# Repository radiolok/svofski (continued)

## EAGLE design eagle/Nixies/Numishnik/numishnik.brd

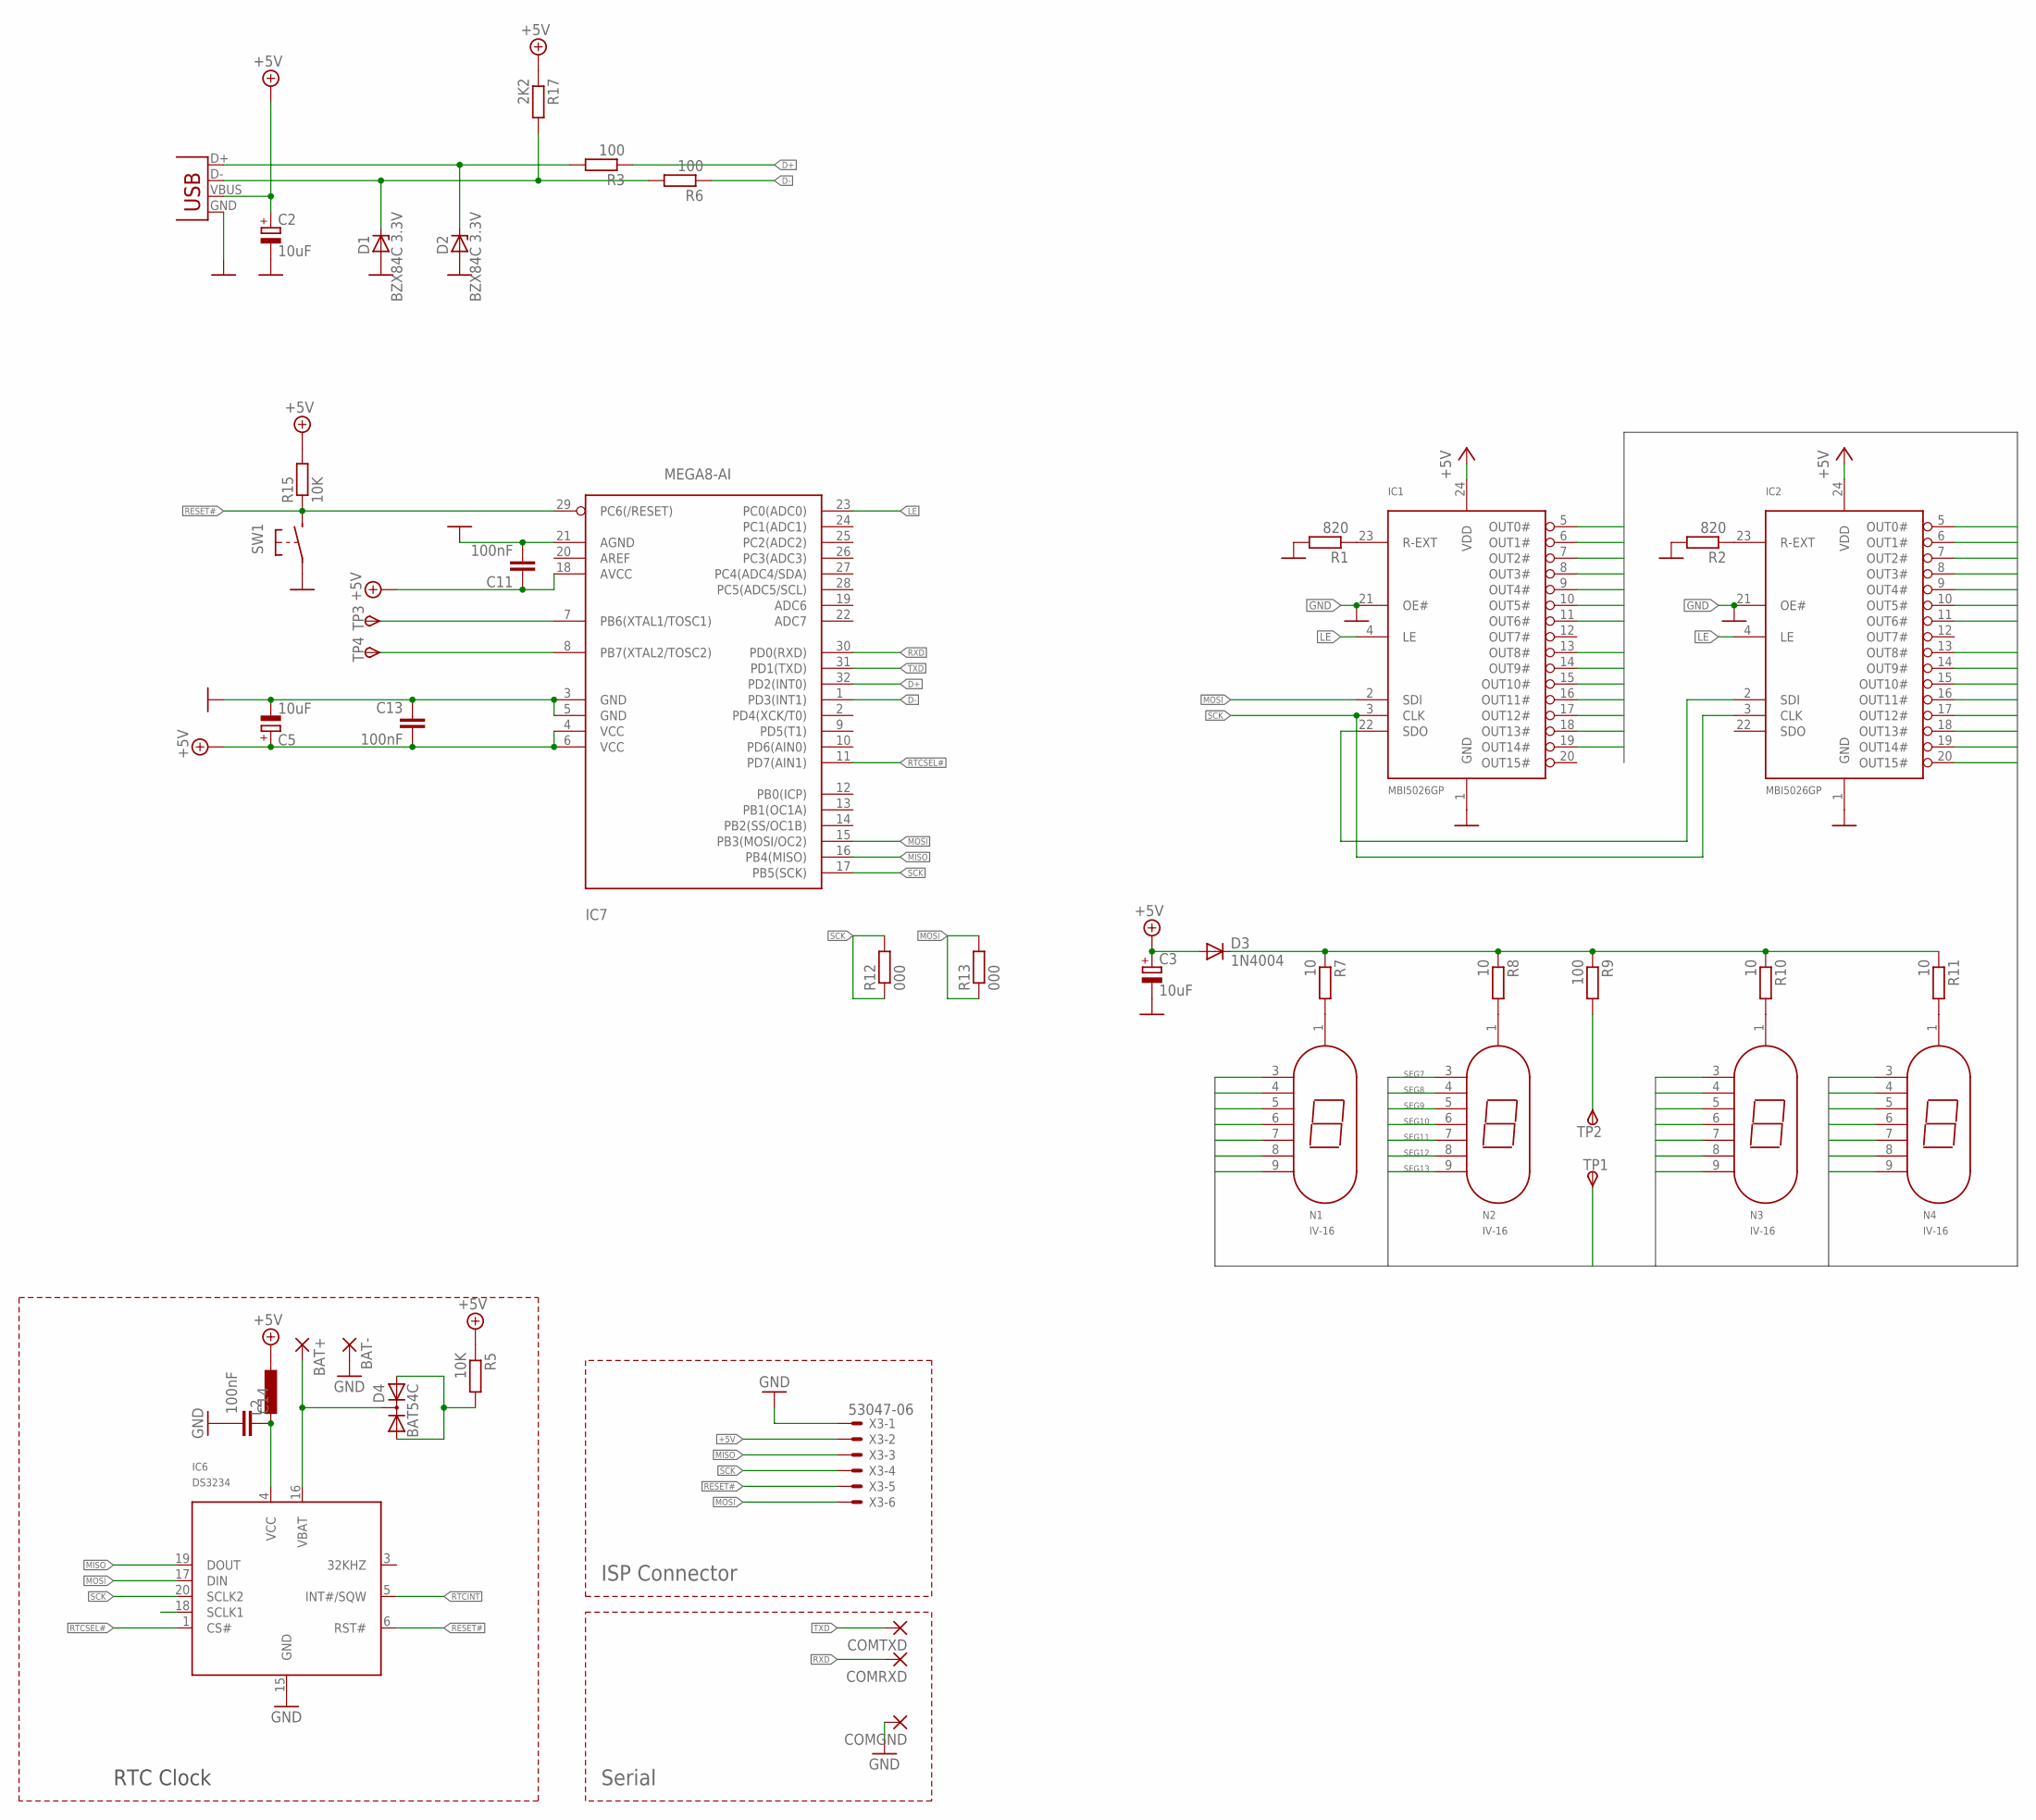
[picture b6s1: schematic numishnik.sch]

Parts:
BAT+: 1,6/0,8
BAT-: 1,6/0,8
C2, C3, C5: 10uF; SMC_B
C11, C13, C14: 100nF; C0603K
COMGND: 1,6/0,8
COMRXD: 1,6/0,8
COMTXD: 1,6/0,8
D1, D2: BZX84C 3.3V; TO236
D3: 1N4004; DO41-10
D4: BAT54C; SOT23
IC1, IC2: MBI5026GP; SSOP24-150
IC6: DS3234; SO-20DW
IC7: MEGA8-AI; TQFP32-08
L2: L-EUL3230M; L3230M
N1, N2, N3, N4: IV-16
R1, R2: 820; R0805-SVO
R3, R6, R9: 100; R0805-SVO
R5, R15: 10K; R0805-SVO
R7, R8, R10, R11: 10; R0805-SVO
R12, R13: 000; R0805-SVO
R17: 2K2; R0805-SVO
SW1: BUTTON-IT_1181; SW_IT1181
TP1, TP2, TP3, TP4: TPSPAD1-13; P1-13
X1: USB-MICROB
X3: 53047-06

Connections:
+5V: C2.+, C3.+, C5.+, C11.1, C13.2, D3.A, IC1.24 (VDD), IC2.24 (VDD), IC7.4 (VCC), IC7.6 (VCC), IC7.18 (AVCC), L2.1, R5.1, R15.2, R17.1, X1.VBUS, X3.2
D+: IC7.32 (PD2(INT0)), R3.1
D-: IC7.1 (PD3(INT1)), R6.1
DOT: IC2.20 (OUT15#), TP1.1
GND: BAT-.1, C2.-, C3.-, C5.-, C11.2, C13.1, C14.2, COMGND.1, D1.A, D2.A, IC1.1 (GND), IC1.21 (OE#), IC2.1 (GND), IC2.21 (OE#), IC6.15 (GND), IC7.3 (GND), IC7.5 (GND), IC7.21 (AGND), R1.2, R2.2, SW1.P$1 (P1), X1.GND, X3.1
LE: IC1.4 (LE), IC2.4 (LE), IC7.23 (PC0(ADC0))
MISO: IC6.19 (DOUT), IC7.16 (PB4(MISO)), X3.3
MOSI: IC1.2 (SDI), IC6.17 (DIN), IC7.15 (PB3(MOSI/OC2)), R13.1, R13.2, X3.6
MOSI#2: IC1.22 (SDO), IC2.2 (SDI)
unnamed: IC7.7 (PB6(XTAL1/TOSC1)), TP3.1
unnamed: R9.2, TP2.1
unnamed: N1.1, R7.2
unnamed: IC1.23 (R-EXT), R1.1
unnamed: IC2.23 (R-EXT), R2.1
unnamed: D1.C, R6.2, R17.2, X1.D-
unnamed: D2.C, R3.2, X1.D+
unnamed: BAT+.1, D4.3 (C), IC6.16 (VBAT)
unnamed: D4.1 (A1), D4.2 (A2), R5.2
unnamed: N2.1, R8.2
unnamed: N3.1, R10.2
unnamed: N4.1, R11.2
unnamed: D3.C, R7.1, R8.1, R9.1, R10.1, R11.1
RESET#: IC6.6 (RST#), IC7.29 (PC6(/RESET)), R15.1, SW1.P$2 (P2), X3.5
RTCINT: IC6.5 (INT#/SQW)
RTCSEL#: IC6.1 (CS#), IC7.11 (PD7(AIN1))
RTCVCC: C14.1, IC6.4 (VCC), L2.2
RXD: COMRXD.1, IC7.30 (PD0(RXD))
SCK: IC1.3 (CLK), IC2.3 (CLK), IC6.20 (SCLK2), IC7.17 (PB5(SCK)), R12.1, R12.2, X3.4
SEG0: IC1.11 (OUT6#), N1.3 (2)
SEG1: IC1.10 (OUT5#), N1.4 (3)
SEG2: IC1.9 (OUT4#), N1.5 (4)
SEG3: IC1.8 (OUT3#), N1.6 (5)
SEG4: IC1.7 (OUT2#), N1.7 (6)
SEG5: IC1.6 (OUT1#), N1.8 (7)
SEG6: IC1.5 (OUT0#), N1.9 (8)
SEG7: IC1.19 (OUT14#), N2.3 (2)
SEG8: IC1.18 (OUT13#), N2.4 (3)
SEG9: IC1.17 (OUT12#), N2.5 (4)
SEG10: IC1.16 (OUT11#), N2.6 (5)
SEG11: IC1.15 (OUT10#), N2.7 (6)
SEG12: IC1.14 (OUT9#), N2.8 (7)
SEG13: IC1.13 (OUT8#), N2.9 (8)
SEG14: IC2.11 (OUT6#), N3.3 (2)
SEG15: IC2.10 (OUT5#), N3.4 (3)
SEG16: IC2.9 (OUT4#), N3.5 (4)
SEG17: IC2.8 (OUT3#), N3.6 (5)
SEG18: IC2.7 (OUT2#), N3.7 (6)
SEG19: IC2.6 (OUT1#), N3.8 (7)
SEG20: IC2.5 (OUT0#), N3.9 (8)
SEG21: IC2.19 (OUT14#), N4.3 (2)
SEG22: IC2.18 (OUT13#), N4.4 (3)
SEG23: IC2.17 (OUT12#), N4.5 (4)
SEG24: IC2.16 (OUT11#), N4.6 (5)
SEG25: IC2.15 (OUT10#), N4.7 (6)
SEG26: IC2.14 (OUT9#), N4.8 (7)
SEG27: IC2.13 (OUT8#), N4.9 (8)
TXD: COMTXD.1, IC7.31 (PD1(TXD))
XTAL2: IC7.8 (PB7(XTAL2/TOSC2)), TP4.1

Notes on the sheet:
ISP Connector
Serial
RTC Clock

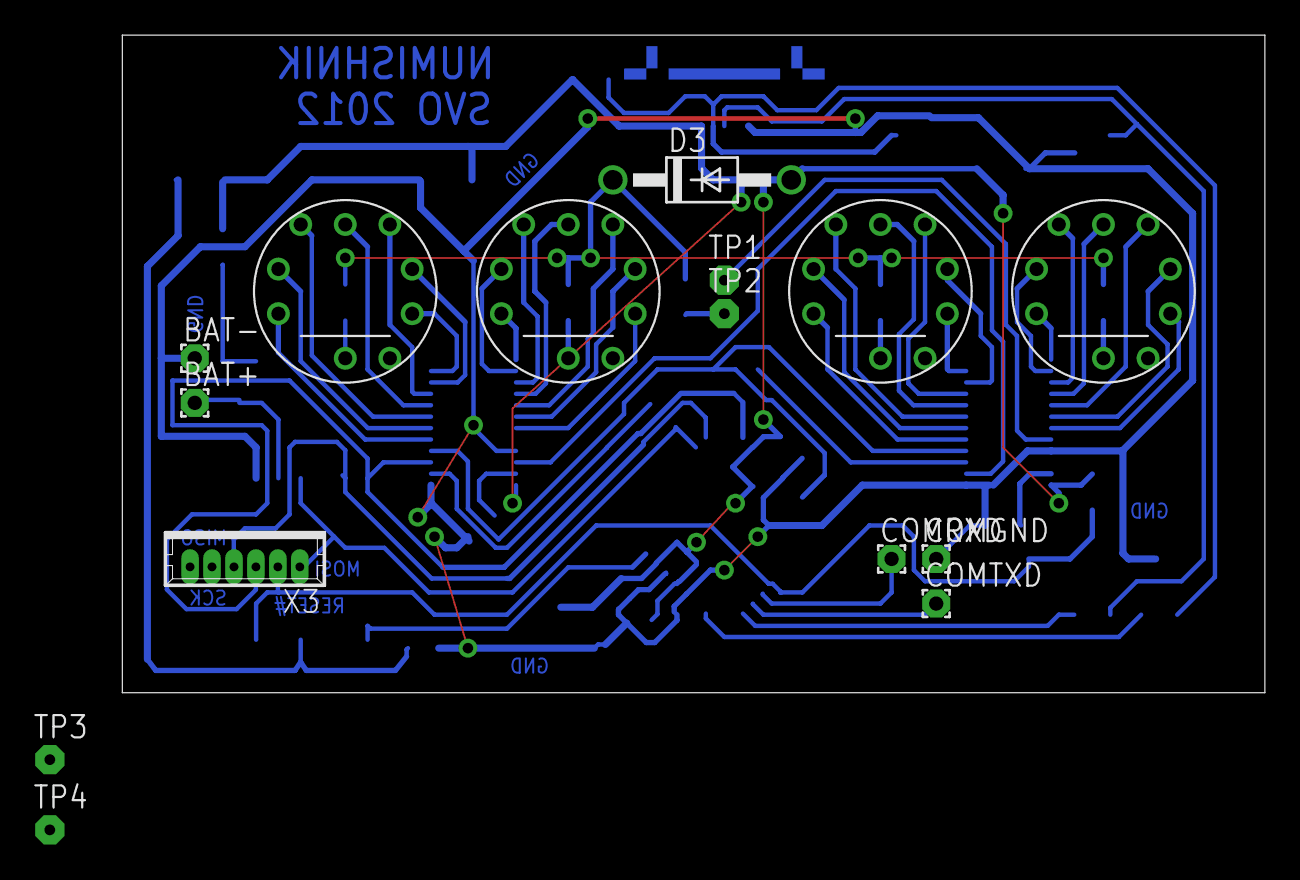
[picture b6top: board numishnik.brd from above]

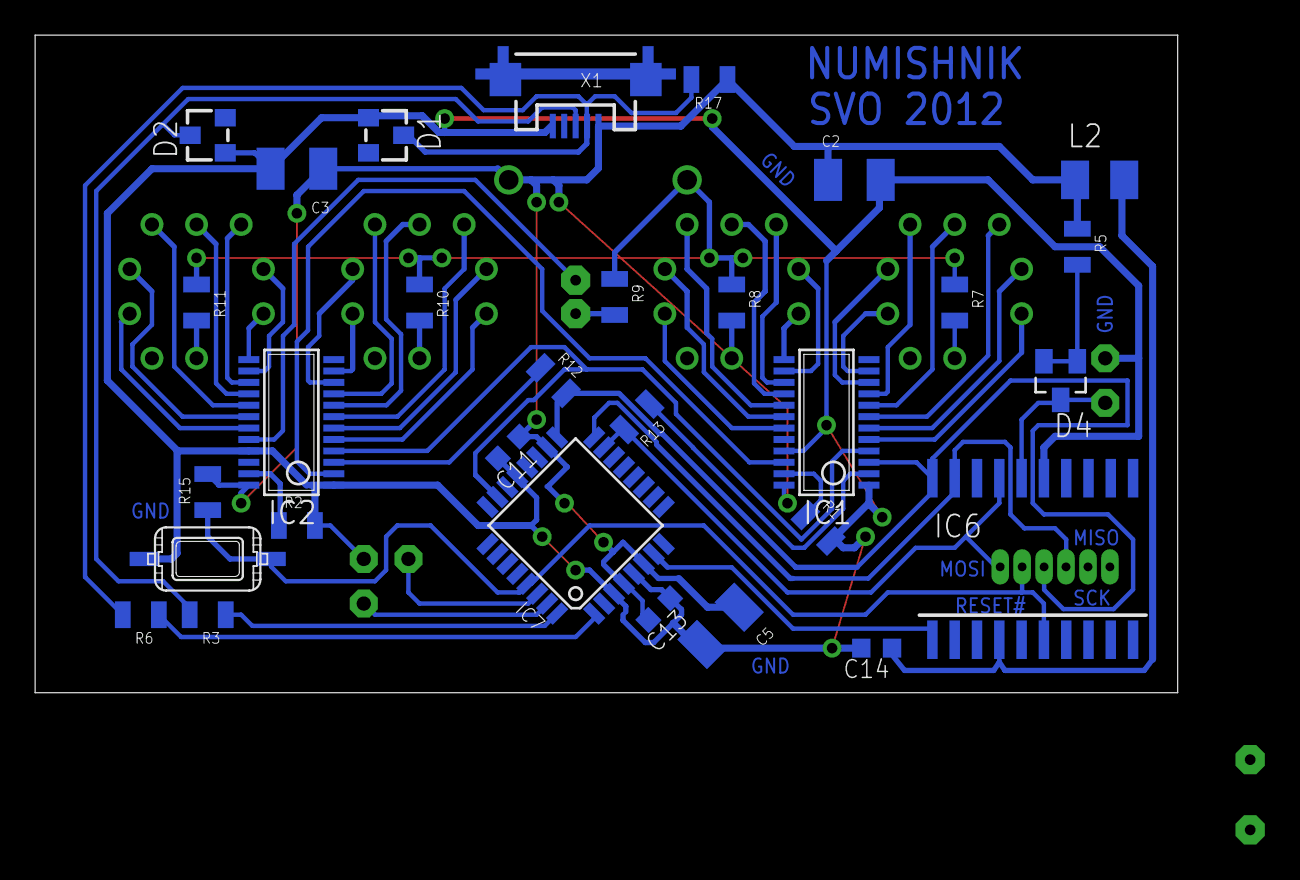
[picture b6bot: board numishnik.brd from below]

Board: 2 copper layers, 65.1 x 37.5 mm, 45 parts (30 on the bottom side), 57 nets.

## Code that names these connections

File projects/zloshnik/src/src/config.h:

#pragma once

#include <avr/io.h>

#define TP(x,y) x ## y 
#define TP2(x,y) TP(x,y)

#define DACSSPORT   C
#define PORT_DACSS  TP2(PORT,DACSSPORT)
#define DDR_DACSS   TP2(DDR,DACSSPORT)
#define DACSS       0
#define DACSS_BV    _BV(DACSS)

#define ZDACPORT    C
#define PORT_ZDAC   TP2(PORT,ZDACPORT)
#define DDR_ZDAC    TP2(DDR,ZDACPORT)
#define ZDAC        1
#define ZDAC_BV     _BV(ZDAC)

#define RTCSSPORT   C
#define PORT_RTCSS  TP2(PORT,RTCSSPORT)
#define DDR_RTCSS   TP2(DDR,RTCSSPORT)
#define RTCSS       2
#define RTCSEL      RTCSS
#define RTCSS_BV    _BV(RTCSS)


#define MOSIPORT    B
#define PORT_MOSI   TP2(PORT,MOSIPORT)
#define DDR_MOSI    TP2(DDR,MOSIPORT)
#define MOSI        PB3
#define MOSIBV      _BV(MOSI)

#define MISOPORT    B
#define PORT_MISO   TP2(PORT,MISOPORT)
#define DDR_MISO    TP2(DDR,MISOPORT)
#define MISO        PB4
#define MISOBV      _BV(MISO)

#define SCKPORT     B
#define PORT_SCK    TP2(PORT,SCKPORT)
#define DDR_SCK     TP2(DDR,SCKPORT)
#define SCK         PB5
#define SCKBV       _BV(SCK)

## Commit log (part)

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2012-03-25 gru..
2012-03-26 +3v3 and conversion for bluetooth, more sparse layout in hv area
2012-03-28 lots of fixes
2012-03-29 stuff
2012-04-01 pcb files (did the board today)
2012-04-01 just updated the board
2012-04-01 se me ha olvidado symbols.inc
2012-04-03 boo..
2012-04-08 stuff!
2012-04-10 increased freq a bit draws a [P]
2012-04-10 just updated los values on the schematic
2012-04-13 some nice stuff
2012-04-13 updates in part values
2012-04-13 first c++ refactoring
2012-04-14 shapes
2012-04-14 cxa, shapes redone, sinus shape the scale is all broken, needs to be redone
2012-04-14 some homemade eagle libs
2012-04-15 grid and stuff
2012-04-16 yay before the vacation state
2012-05-13 latest fixes for 3loshnik schematics
    morsekeyer
2012-05-13 zloshnik
2012-05-13 morseshnik: initial crap
2012-08-07 incursion first rev
2012-08-07 ship sprite: no line-optimization
2012-08-08 keep 0 in reg, use h
2012-08-11 makesprites ltr, rtl and inf/sup moving test (without inf/sup)
2012-08-12 inf works and test
2012-08-12 bouncing ship, sprite always pointing right
2012-08-12 bouncing good, limits shown
2012-08-12 test with 5 ships
2012-08-13 + descriptor has pointers to dispatch tables + helicopter and propeller animation
2012-08-14 only cleanup
2012-08-14 foes by id, propeller as child of copter time marks
    time for 7 foes: 5.5
2012-08-14 fast copyfoe/copyback
2012-08-14 time average reduced to 3.5 size reduced by ~1k thanks to sprite optimizations
2012-08-15 new palette: 7 colours + black for clipping scroll clipping
2012-08-16 fixed bug in the assembler: $3d now works in equ
    added blinds on the sides: for the airplanes
2012-08-16 plane
    experimental code that has variable direction value
    not working very well, to be replaced with separate
    code for the jet
2012-08-16 cleaned up foe-bounce part
2012-08-16 planes flying, but on the right there's a problem with clipping
2012-08-17 fixed jet clipping on the right
2012-08-17 fixed clearblinds not to overrun when on edge of screen fixed scratch area for all sprites moved foeBounce flag into H
2012-08-17 rearranged foeBlock so that only 4 bytes need to be copied back
2012-08-17 integrated copyfoe/copyback into foe_in_hl
2012-08-18 removed all sprite_scratch, changed frame restore to lxi sp
2012-08-18 little silly optimizations
2012-08-18 shaved off 16 cycles from copyfoe/copyback
2012-08-18 optimization in clearblinds
2012-08-18 test river bank
2012-08-18 some very rough terrain
2012-08-18 slightly smoother terrain
2012-08-18 foes get discarded and wiped at the bottom of the screen
2012-08-18 needs randomNormA
2012-08-18 random generated foes in terrain, working well
2012-08-19 tweaked the ship graphics to make it less jumpy when turning around
2012-08-19 some cleanup before the island work
2012-08-21 enemies temporarily disabled
    island generation works, but the resulting passages are too narrow
2012-08-23 no narrow passages!
2012-08-23 started bridge generation work crashes at 2nd bridge if the enemies are turned on
2012-08-25 some cleanups road generation foe generation crashes
2012-08-25 not without some bad crap but: + road + restored most of foe generation + added left/water buffers for dynamic foe bounces - not sure if needed
2012-08-25 moved bounce boundaries retrieval to foe generation: this is possible thanks to having terrain already generated foe update cycle now does not update the boundaries
2012-08-25 added bridge, but it's crappy
2012-08-26 navigation in pretty assembler (unfinished)
2012-08-26 lots of navigational and style fixes
2012-08-27 some stuff towards highlightable registers, not yet complete
2012-08-28 register highlighting
2012-08-28 - console output in navigate.js + debug border on different parts of update in incursion.asm
2012-08-28 scrolling fixes
2012-08-28 bridges! #10 fails on screen overlap though...
2012-08-28 bridges are good
2012-08-30 fuel work started
2012-08-30 .list and .nolist in assembler
2012-08-30 +palette.inc
2012-08-30 moved all variables in a single place
2012-08-30 only comment formatting
2012-08-31 made foe_clearance to make foes less even, block update also updates clearance to be large enough to avoid copters ramming the ground. it still happens sometimes
    almost acceptable playfield, except that the fuel often overlaps the banks
2012-09-02 just some cleanup, removed unused junk
2012-09-02 restructured the subroutines
2012-09-02 more basic structure/readability changes
2012-09-02 more cleanup
2012-09-02 moved variables into variables.inc going to make terrain_next2
2012-09-03 no fuel overlaps!
2012-09-03 old uncommitted changes in morsekeyer/src/main.c
2012-09-03 closing head 198
2012-09-03 closing branch snuu
2012-09-03 closing branch newmakefile-for-numishnik
2012-09-03 closing branch numishnik-wtf
2012-09-04 player draft
2012-09-06 crappy input
2012-09-06 great player X movement made fuel narrower
2012-09-06 plane shape bottom cutoff lowered by 8 to avoid plane scratching the fuel
2012-09-06 fine speed control, sound
2012-09-08 player collision detection
2012-09-08 separate routine for wiping without collision detection
2012-09-08 some (probably stupid) optimizations
2012-09-08 some more cleanup
2012-09-08 shaved 32 (32*8=256!) cycles in copyback
2012-09-08 20 cycles per copyfoe less == 416 total per 8 foes compared to penultimate revision
2012-09-09 missile
2012-11-02 zloshnik circuit update (cosmetic)
2012-11-13 biquad experiments
2012-12-15 initial commit of fapubar
2012-12-18 nice 20 biquads
2012-12-18 restored bode plot calculation
2012-12-19 on/off logic for the boost gen, works RIP IRF7450
2012-12-20 make sure that pwm is not just stopped but paused when the output is 0
2012-12-20 sync
2012-12-20 +gpio
2012-12-20 bargraphs gpio setup
2012-12-22 working bar #19 test
2013-01-07 fixed spikes: they happened when peak values were 0
2013-01-09 implemented decimation for 2 bottom bands: now the Q is always 10, nice display
2013-01-13 freq = 26500, 26000 seems to have funny beats with the bargraph pwm
2013-05-30 SPY.COM disasm
2013-06-05 refactoring ncopy
2013-06-05 upsie daisy
2013-06-05 wrapped all packets used in ncopy
2013-06-05 sendFile func
2013-06-06 implemented large part of send.c in ncopy getopt used for more sophisticated options only the most basic ROM sending is implemented
2013-06-07 separated send/basic stuff into netsend, cpm into ncopy
    msxnet is the main module now
2013-06-08 nicer messages --cpm works together with multiple files bin loading works multipart rom loading works tested on KNIGHT.ROM and Vampire Killer
2013-06-08 uupsie doodle
2013-06-08 BASIC sending implemented POKE implemented
2013-06-08 renamed netsend -> basicsend, wrapped netsend functionality in BasicSender class reverted pingPong() to wait as much as needed
2013-06-10 stuff loads fine but command.com or other real programs would not run
2013-06-16 a huge mess but it is able to upload COMMAND.COM, serve requested AUTOEXEC.BAT and die when it tries to search first (provided that AUTOEXEC.BAT contains DIR command)
2013-06-17 +spy DBG.COM can be uploaded and a debuggee program can be loaded via ESC+I
2013-06-17 implemented search first/next using glob(), does not really work well: glob is not good for ???????.??? patterns
2013-06-23 ton of changes.. zork1 loads!
2013-06-23 turbo pascal loads: implemented fake BIOS jumptable. does not work too well really without fancy terminal i/o
    some source code housekeeping
    SendPacket(*) -> SendPacket(&)
2013-06-23 "implemented" 1B - get allocation information. it really should be redone in the bdos part
2013-06-26 save IX/IY -- turbo pascal now works!
    todo: implement decent NOP on nonexistent msxdos functions. now we die when TP tries to call function 1F
2013-06-27 mostly fixed console i/o routines, ladder.com works now
2013-06-29 readline from msx-dos, now command.com can handle one command
2013-06-29 implemented dos-like glob for directory
2013-06-29 fix for zero-sized data chunks
2014-01-11 +cartuchnik
2014-01-12 making a disk in progmem
2014-01-12 linker script shenanigans for IAP: reserve top 32 bytes
2014-01-15 terribly dirty but mass storage works in program flash, can be formatted
2014-01-15 fixed files crossing flash sector borders some code cleanup
2014-01-16 added loader select routine + Elm's PFF
2014-01-19 some basic makefile for C + crt0.S
    6809 gcc by Brian Dominy (bcd) from:
    https://github.com/bcd/gcc
    https://github.com/bcd/newlib-6809
    crt0.S thanks to Frank Buss http://www.frank-buss.de/vectrex/
2014-01-22 some progress with title selector
2014-01-22 more selector stuff, decorations
2014-01-22 smooth star jumping between items
2014-01-23 code cleanup, split off bios routines to vectrex.S
2014-01-23 pages
2014-01-24 fun animations
2014-01-24 menu more or less done, needs select function and actual launcher
2014-01-25 more menu fancy
2014-01-25 moar menu
2014-01-25 added bss initialization bss moved to proper 0xc880
2014-02-01 lowered frame rate various optimizations - less divisions etc, slightly faster updates
2014-02-01 firmware: prepare file list for the loader loader: show actual files
2014-02-03 +loader.c/h menu fixes in the loader
2014-04-03 updates to support encoding
2014-04-03 moved offline assembler to a separate dir
2014-04-03 moved asm to prettyasm dir, update makefile to create links
2014-04-03 sample + encodings
2014-04-07 python version of pretty assembler
2014-04-10 pythonification of pasm.py
2014-04-10 moar...
2014-04-10 a bit moar...
2014-04-11 some beton
2014-04-11 momor
2014-04-11 glob
2014-04-11 more strings -> lists for delayed joining
2014-04-11 separated IntelHex and MemoryDump
2014-04-11 packed lengths, addrs, refs, textlabels, flags into LineData
2014-04-11 listOff in flags
2014-04-11 separated Resolver
2014-04-11 fixed or | in .js fixed expression evaluator
2014-04-11 navigate.js: fixed backref highlight when line has comment hex dump: skip undefined bytes in character area in useExpr() reference labels using evaluateExpr(), thus marking individual labels used in 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
2014-04-11 stylistic mumbo
2014-04-15 new play parser
2014-04-15 oops tokens->cdr
2014-04-16 support ' and " literals
2014-04-16 tokenized arguments
2015-01-13 fixed mixed case labels fixed uppercase registers
2015-01-20 fixed substituteBitwiseOps fixed missing class ref in markLabel calls
2015-01-21 p2 tests
2015-01-21 more tests, start of file reader
2015-01-22 fixed ldax/stax with incorrect register pairs
2015-01-22 always drop comments
2015-01-25 polishificator
2015-03-09 checking in random stuff
2015-03-09 attempt to make software pwm for quieter motor
2015-07-13 Migrating wiki contents from Google Code
